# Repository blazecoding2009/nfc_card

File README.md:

# NFC Hacker Card

Simple card I made in KiCad, had to make the antenna and stuff myself as there are none publically available

Has an LED on it to show it is working and should cost $25 to make 5 of them

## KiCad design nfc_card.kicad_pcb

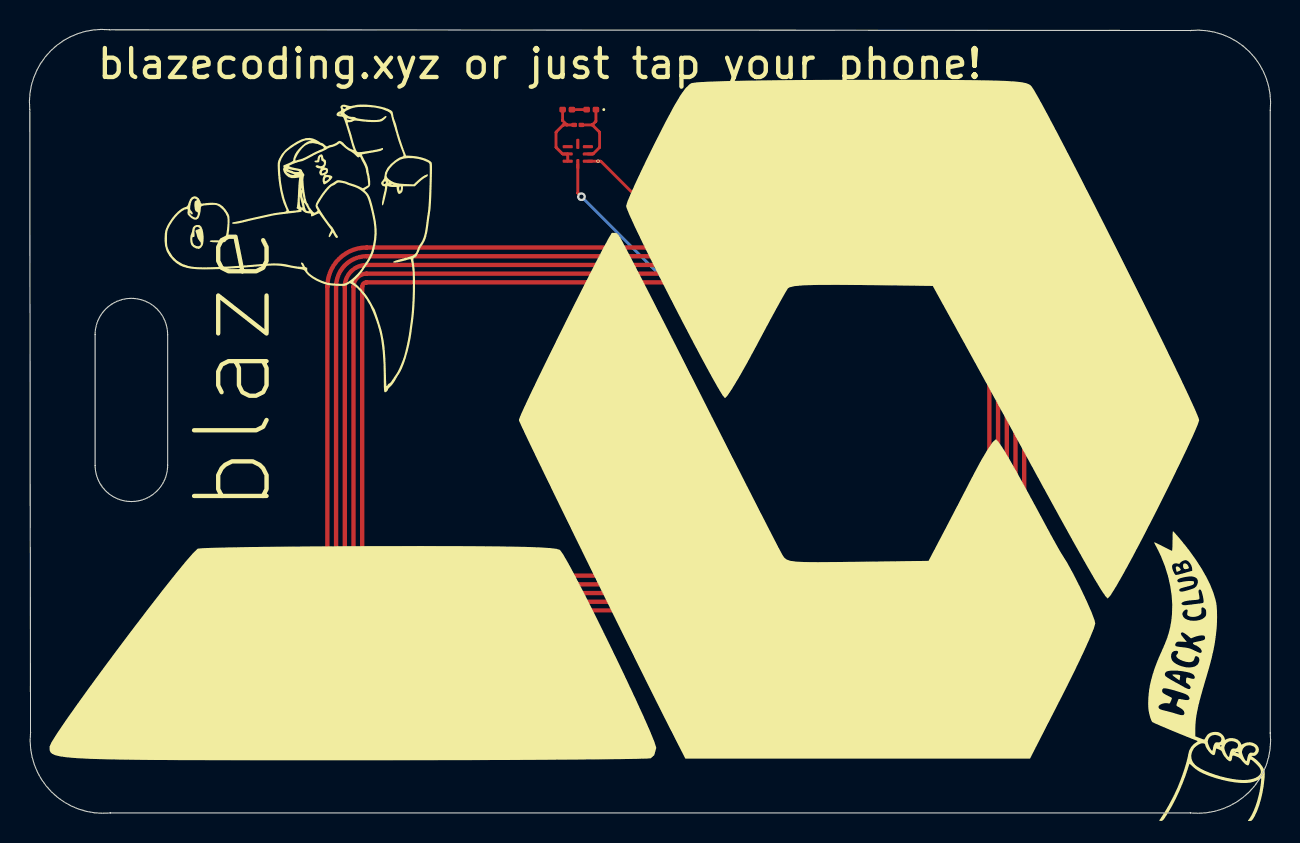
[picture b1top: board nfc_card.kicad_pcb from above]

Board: 2 copper layers, 85.5 x 54.0 mm, 5 parts (0 on the bottom side), 5 nets.

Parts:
C1: 220nf; C_01005_0402Metric
D1: LED; LED_0201_0603Metric
R1: 47ohm; R_0201_0603Metric
U1: NT3H2111W0FHKH; QFN8P50_160X160X50L40X20N
U2: NFC_ANTENNA; 25X48MM_NFC_ANTENNA

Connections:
unnamed: D1.2 (A), R1.1
unnamed: C1.2, D1.1 (K), U1.2 (VSS)
unnamed: U1.1 (LA), U2.P$1
unnamed: U1.8 (LB), U2.P$2
unnamed: C1.1, R1.2, U1.6 (VCC), U1.7 (VOUT)

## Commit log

2024-08-13 init commmmmmmittttttttt!
2024-08-13 routing!
2024-08-15 a bit of work
2024-08-15 stufffff
2024-08-15 bit of design, needs to be finished
2024-08-17 graphics!
2024-08-17 swithing back to old nfc
2024-08-19 clen up!
2024-08-19 almost done, one more session to go
2024-08-19 yay i think im finished
